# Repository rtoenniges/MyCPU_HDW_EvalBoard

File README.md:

# MyCPU_HDW_EvalBoard
An evaluation board for the [MyCPU](http://www.mycpu.eu/) that splits the many signals from the backplane bus to handy connectors.

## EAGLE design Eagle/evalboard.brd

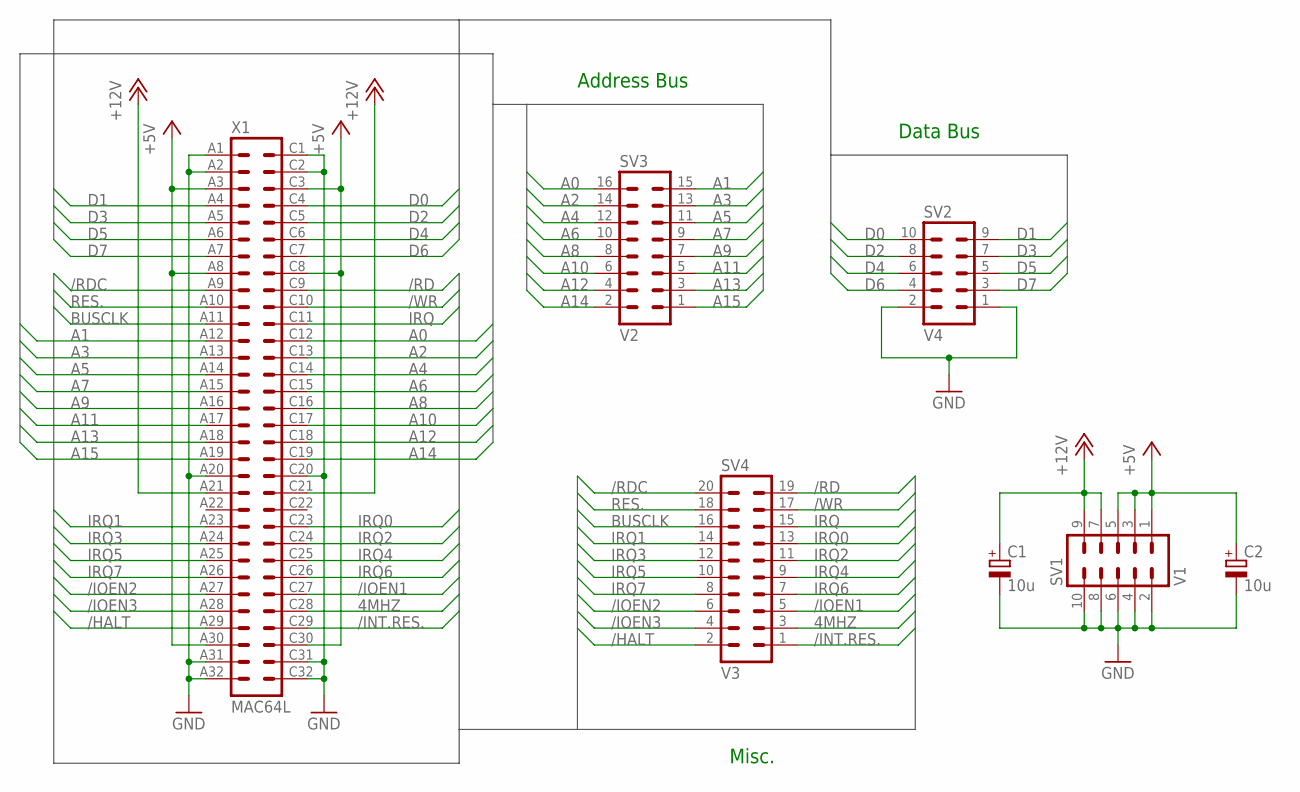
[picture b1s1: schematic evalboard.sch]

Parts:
C1, C2: 10u; E2,5-5
SV1: V1; ML10L
SV2: V4; ML10L
SV3: V2; ML16L
SV4: V3; ML20L
X1: MAC64L

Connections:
4MHZ: SV4.3, X1.C28
+5V: C2.+, SV1.1, SV1.3, SV1.5, X1.A3, X1.A8, X1.A30, X1.C3, X1.C8, X1.C30
+12V: C1.+, SV1.7, SV1.9, X1.A21, X1.C21
/HALT: SV4.2, X1.A29
/INT.RES.: SV4.1, X1.C29
/IOEN1: SV4.5, X1.C27
/IOEN2: SV4.6, X1.A27
/IOEN3: SV4.4, X1.A28
/RD: SV4.19, X1.C9
/RDC: SV4.20, X1.A9
/WR: SV4.17, X1.C10
A0: SV3.16, X1.C12
A1: SV3.15, X1.A12
A2: SV3.14, X1.C13
A3: SV3.13, X1.A13
A4: SV3.12, X1.C14
A5: SV3.11, X1.A14
A6: SV3.10, X1.C15
A7: SV3.9, X1.A15
A8: SV3.8, X1.C16
A9: SV3.7, X1.A16
A10: SV3.6, X1.C17
A11: SV3.5, X1.A17
A12: SV3.4, X1.C18
A13: SV3.3, X1.A18
A14: SV3.2, X1.C19
A15: SV3.1, X1.A19
BUSCLK: SV4.16, X1.A11
D0: SV2.10, X1.C4
D1: SV2.9, X1.A4
D2: SV2.8, X1.C5
D3: SV2.7, X1.A5
D4: SV2.6, X1.C6
D5: SV2.5, X1.A6
D6: SV2.4, X1.C7
D7: SV2.3, X1.A7
GND: C1.-, C2.-, SV1.2, SV1.4, SV1.6, SV1.8, SV1.10, SV2.1, SV2.2, X1.A1, X1.A2, X1.A20, X1.A31, X1.A32, X1.C1, X1.C2, X1.C20, X1.C31, X1.C32
IRQ: SV4.15, X1.C11
IRQ0: SV4.13, X1.C23
IRQ1: SV4.14, X1.A23
IRQ2: SV4.11, X1.C24
IRQ3: SV4.12, X1.A24
IRQ4: SV4.9, X1.C25
IRQ5: SV4.10, X1.A25
IRQ6: SV4.7, X1.C26
IRQ7: SV4.8, X1.A26
RES.: SV4.18, X1.A10

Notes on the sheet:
Address Bus
Data Bus
Misc.

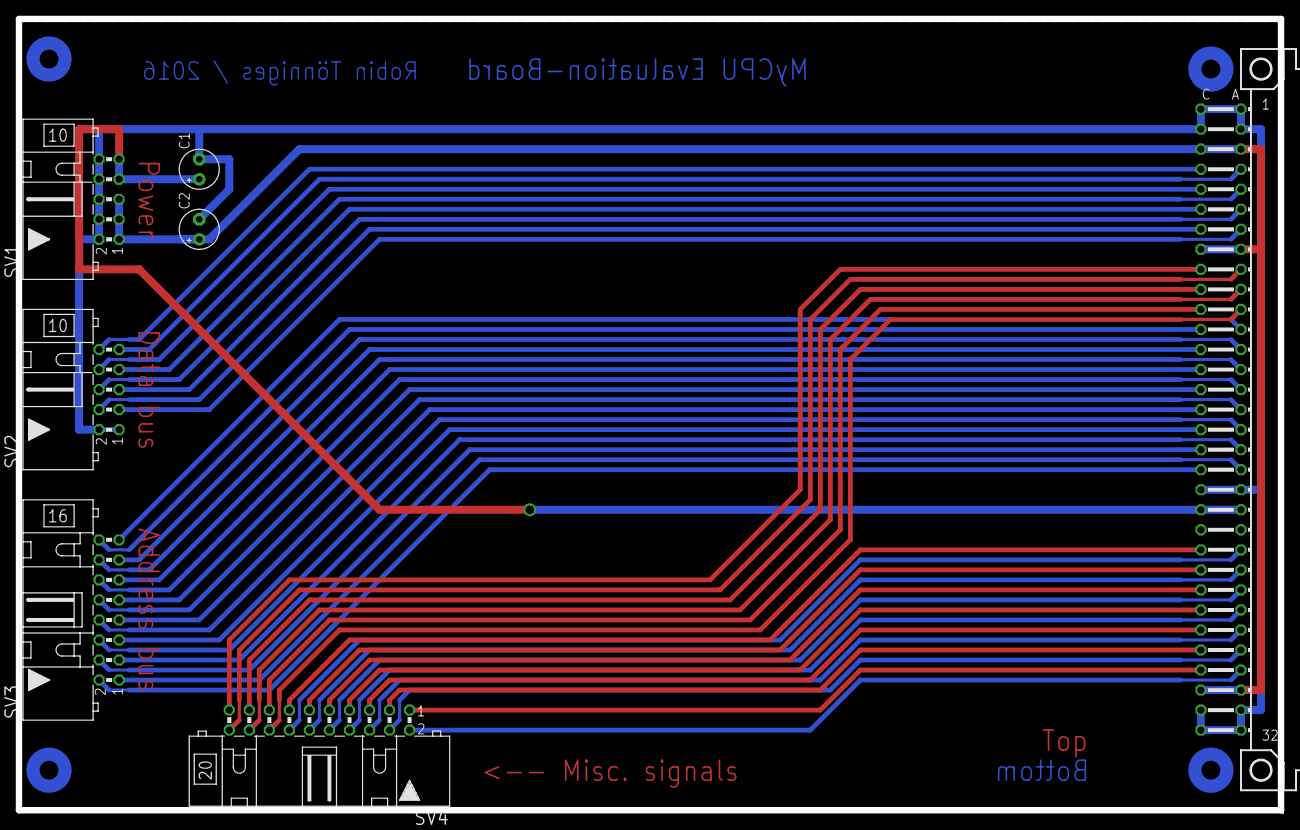
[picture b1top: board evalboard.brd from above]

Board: 2 copper layers, 160.0 x 100.3 mm, 7 parts (0 on the bottom side), 47 nets.

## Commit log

2016-10-18 First release
2016-10-18 Added placement diagram
2017-02-20 Schematic and layout changes
    Added two additional tantal caps for 5V and 12V lines.
2017-03-20 Added licence
